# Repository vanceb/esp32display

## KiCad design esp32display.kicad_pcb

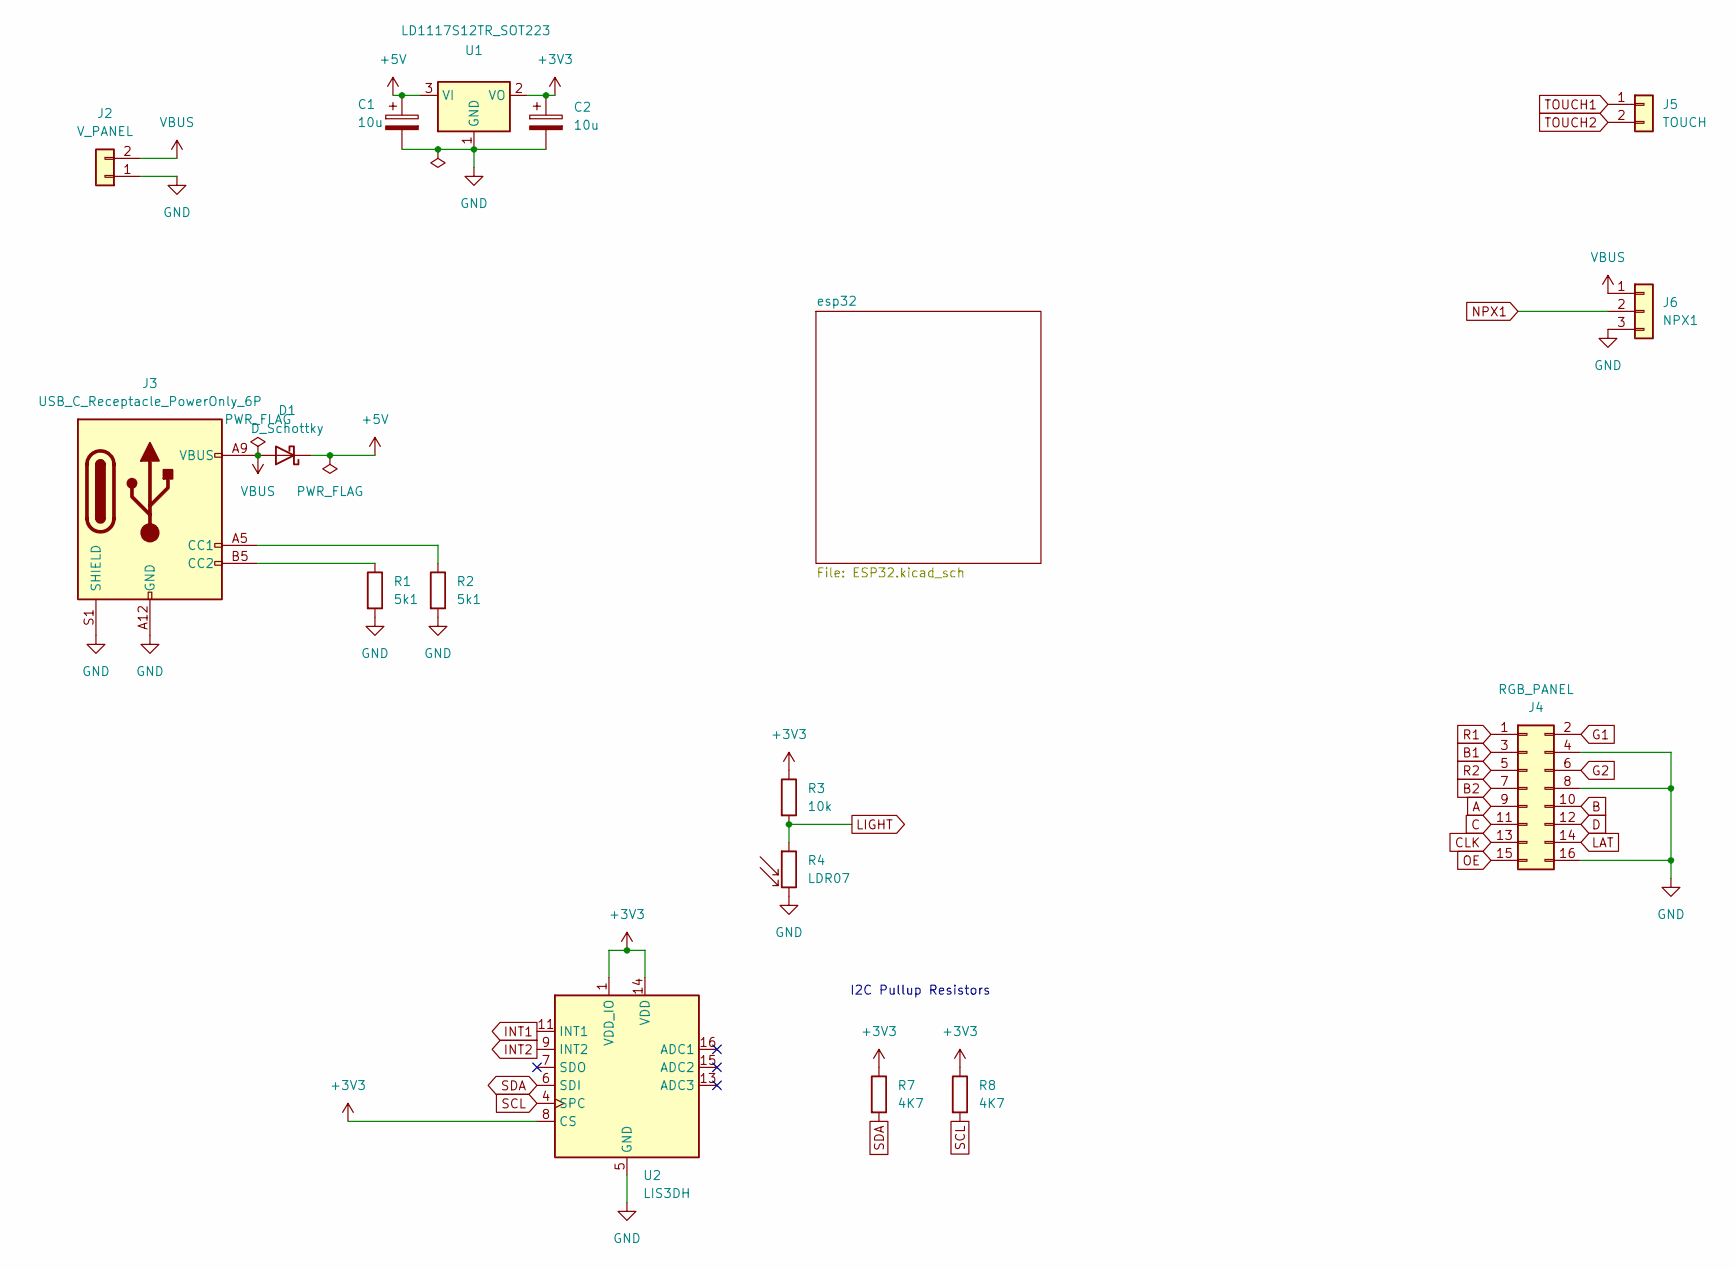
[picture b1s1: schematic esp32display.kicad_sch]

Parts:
C1, C2: 10u; C_0805_2012Metric; LCSC C13585
D1: D_Schottky; D_SMA; LCSC C14996
J2: V_PANEL; PinHeader_1x02_P2.54mm_Vertical
J3: USB_C_Receptacle_PowerOnly_6P; USB_C_Receptacle_GCT_USB4125-xx-x_6P_TopMnt_Horizontal; LCSC C2689837
J4: RGB_PANEL; IDC-Header_2x08_P2.54mm_Vertical
J5: TOUCH; JST_PH_S2B-PH-K_1x02_P2.00mm_Horizontal
J6: NPX1; JST_PH_S3B-PH-K_1x03_P2.00mm_Horizontal
R1, R2: 5k1; R_0603_1608Metric_Pad0.98x0.95mm_HandSolder; LCSC C23186
R3: 10k; R_0603_1608Metric_Pad0.98x0.95mm_HandSolder; LCSC C25804
R4: LDR07; JST_PH_S2B-PH-K_1x02_P2.00mm_Horizontal
R7, R8: 4K7; R_0603_1608Metric_Pad0.98x0.95mm_HandSolder
U1: LD1117S12TR_SOT223; SOT-223-3_TabPin2
U2: LIS3DH; LGA-16_3x3mm_P0.5mm_LayoutBorder3x5y

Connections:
+3V3: C2.1, R3.1, R7.1, R8.1, U1.2 (VO), U2.1 (VDD_IO), U2.8 (CS), U2.14 (VDD); also elsewhere on the board
+5V: C1.1, D1.1 (K), U1.3 (VI)
A: J4.9; also elsewhere on the board
B: J4.10; also elsewhere on the board
B1: J4.3; also elsewhere on the board
B2: J4.7; also elsewhere on the board
C: J4.11; also elsewhere on the board
CLK: J4.13; also elsewhere on the board
D: J4.12; also elsewhere on the board
G1: J4.2; also elsewhere on the board
G2: J4.6; also elsewhere on the board
GND: C1.2, C2.2, J2.1, J3.A12 (GND), J3.B12 (GND), J3.S1 (SHIELD), J4.4, J4.8, J4.16, J6.3, R1.2, R2.2, R4.2, U1.1 (GND), U2.5 (GND), U2.10 (GND), U2.12 (GND); also elsewhere on the board
INT1: U2.11 (INT1); also elsewhere on the board
INT2: U2.9 (INT2); also elsewhere on the board
LAT: J4.14; also elsewhere on the board
LIGHT: R3.2, R4.1; also elsewhere on the board
NPX1: J6.2; also elsewhere on the board
unnamed: J3.A5 (CC1), R2.1
unnamed: J3.B5 (CC2), R1.1
OE: J4.15; also elsewhere on the board
R1: J4.1; also elsewhere on the board
R2: J4.5; also elsewhere on the board
SCL: R8.2, U2.4 (SPC); also elsewhere on the board
SDA: R7.2, U2.6 (SDI); also elsewhere on the board
TOUCH1: J5.1; also elsewhere on the board
TOUCH2: J5.2; also elsewhere on the board
VBUS: D1.2 (A), J2.2, J3.A9 (VBUS), J3.B9 (VBUS), J6.1

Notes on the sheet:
I2C Pullup Resistors

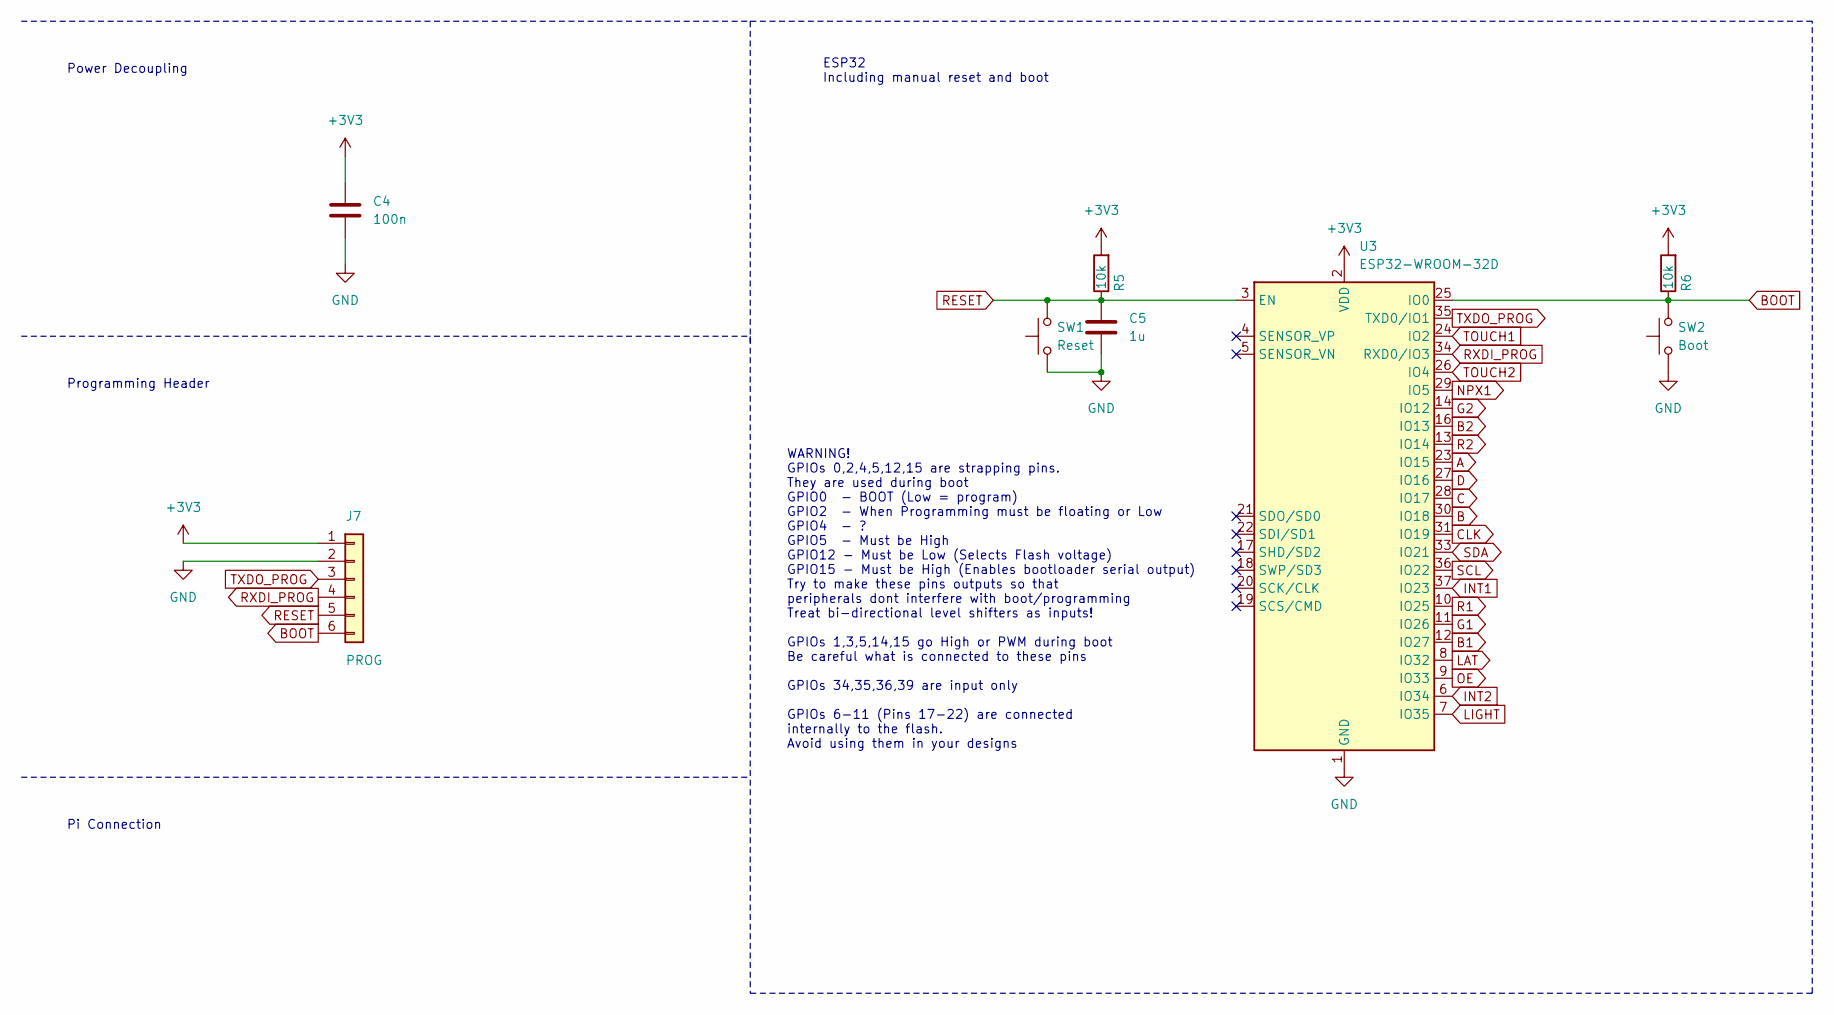
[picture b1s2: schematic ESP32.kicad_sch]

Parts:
C4: 100n; C_0603_1608Metric; LCSC C14663
C5: 1u; C_0603_1608Metric; LCSC C15849
J7: PROG; PinHeader_1x06_P2.54mm_Vertical
R5, R6: 10k; R_0603_1608Metric_Pad0.98x0.95mm_HandSolder; LCSC C25804
SW1: Reset; SW_Push_1P1T_XKB_TS-1187A
SW2: Boot; SW_Push_1P1T_XKB_TS-1187A
U3: ESP32-WROOM-32D; LCSC C473012

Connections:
+3V3: C4.1, J7.1, R5.2, R6.2, U3.2 (VDD); also elsewhere on the board
A: U3.23 (IO15); also elsewhere on the board
B: U3.30 (IO18); also elsewhere on the board
B1: U3.12 (IO27); also elsewhere on the board
B2: U3.16 (IO13); also elsewhere on the board
BOOT: J7.6, R6.1, SW2.2, U3.25 (IO0)
C: U3.28 (IO17); also elsewhere on the board
CLK: U3.31 (IO19); also elsewhere on the board
D: U3.27 (IO16); also elsewhere on the board
G1: U3.11 (IO26); also elsewhere on the board
G2: U3.14 (IO12); also elsewhere on the board
GND: C4.2, C5.2, J7.2, SW1.1, SW2.1, U3.1 (GND), U3.15 (GND), U3.38 (GND), U3.39 (GND); also elsewhere on the board
INT1: U3.37 (IO23); also elsewhere on the board
INT2: U3.6 (IO34); also elsewhere on the board
LAT: U3.8 (IO32); also elsewhere on the board
LIGHT: U3.7 (IO35); also elsewhere on the board
NPX1: U3.29 (IO5); also elsewhere on the board
OE: U3.9 (IO33); also elsewhere on the board
R1: U3.10 (IO25); also elsewhere on the board
R2: U3.13 (IO14); also elsewhere on the board
RESET: C5.1, J7.5, R5.1, SW1.2, U3.3 (EN)
RXDI_PROG: J7.4, U3.34 (RXD0/IO3)
SCL: U3.36 (IO22); also elsewhere on the board
SDA: U3.33 (IO21); also elsewhere on the board
TOUCH1: U3.24 (IO2); also elsewhere on the board
TOUCH2: U3.26 (IO4); also elsewhere on the board
TXDO_PROG: J7.3, U3.35 (TXD0/IO1)

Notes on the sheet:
Pi Connection
ESP32 Including manual reset and boot
Programming Header
WARNING! GPIOs 0,2,4,5,12,15 are strapping pins. They are used during boot GPIO0 - BOOT (Low = program) GPIO2 - When Programming must be floating or Low GPIO4 - ? GPIO5 - Must be High GPIO12 - Must be Low (Selects Flash voltage) GPIO15 - Must be High (Enables bootloader serial output) Try to make t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
Power Decoupling

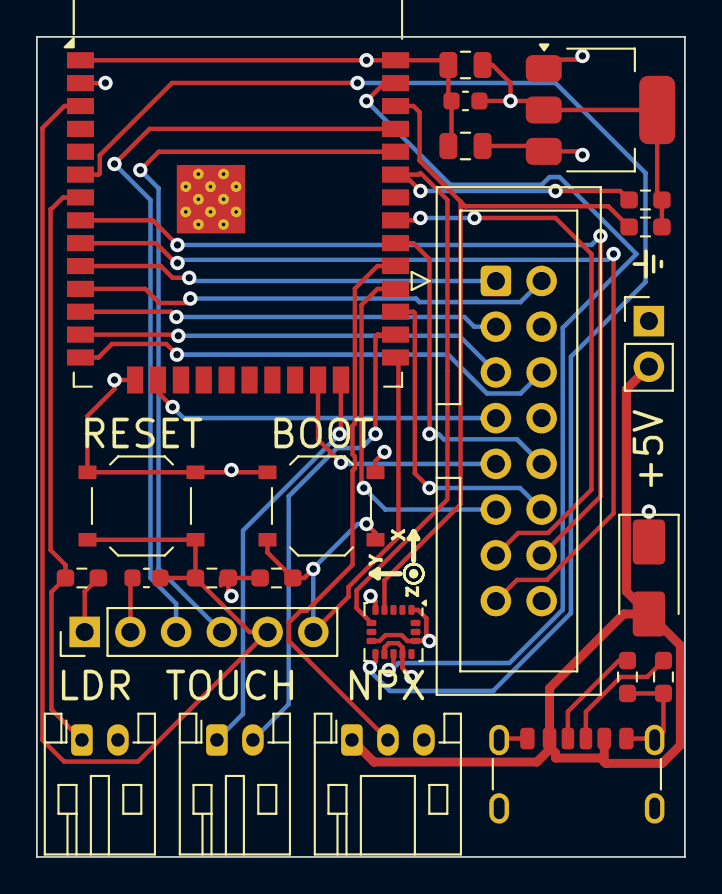
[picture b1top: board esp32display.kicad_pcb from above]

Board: 4 copper layers, 36.0 x 45.6 mm, 24 parts (0 on the bottom side), 31 nets.

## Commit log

2022-12-19 Gerbers for V0.1 Production
2024-10-10 Work in progress
2024-10-28 Added .gitignore for kicad project
2024-10-28 Started to change project in preparation for next version
2024-11-01 Submitted V0.2 to production
2024-11-01 Added I2C Pullup Resistors
2024-11-14 Minor fixes from V0.2. Corrected C1 & C2 package sizes. Improved pushbutton marking on silkscreen.
